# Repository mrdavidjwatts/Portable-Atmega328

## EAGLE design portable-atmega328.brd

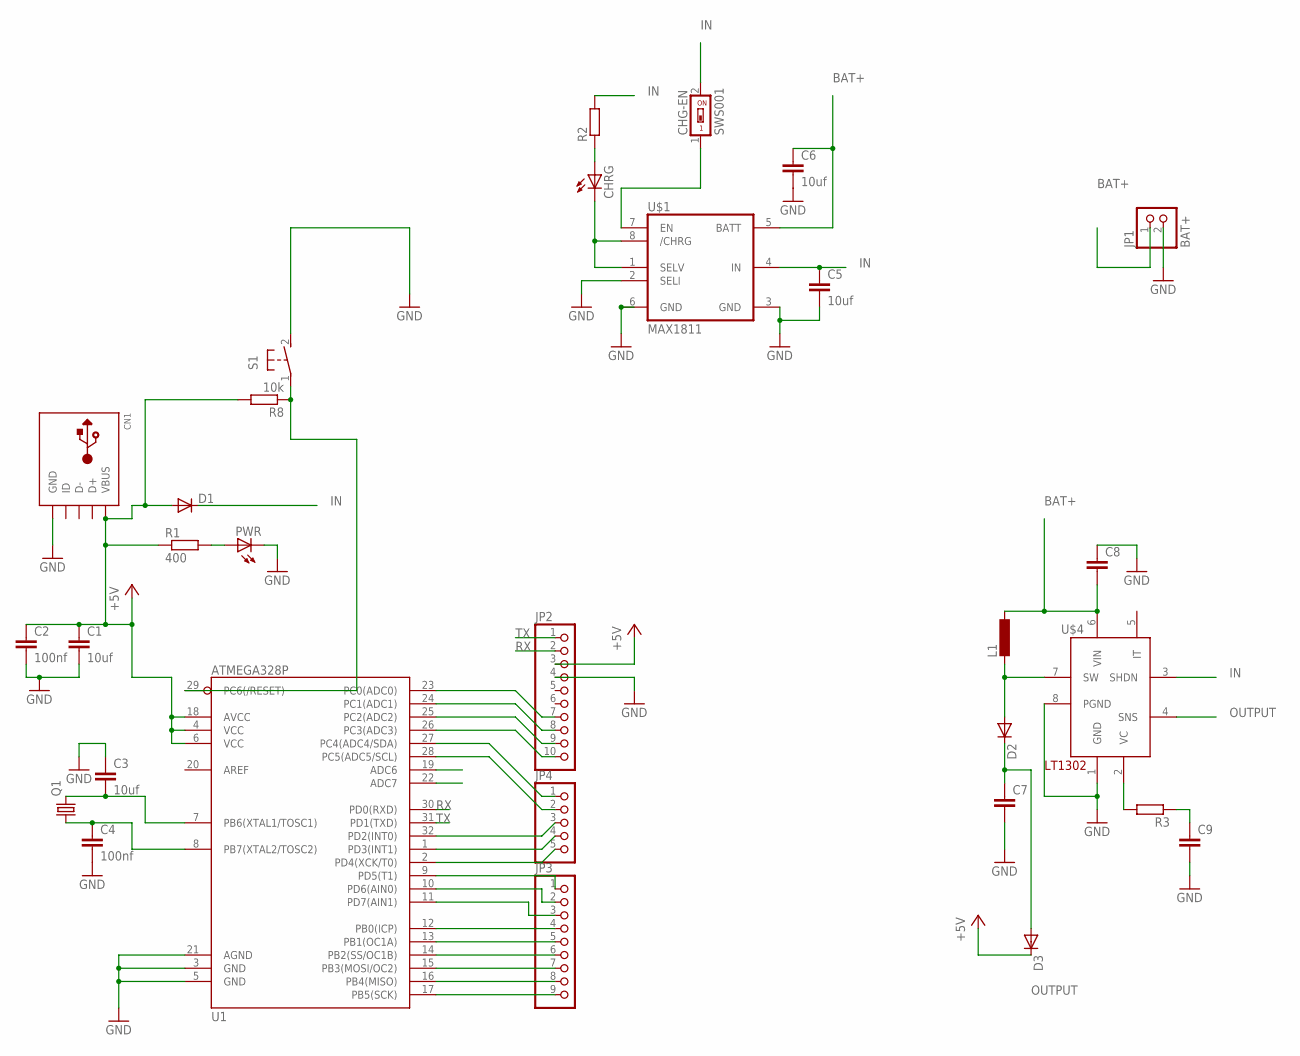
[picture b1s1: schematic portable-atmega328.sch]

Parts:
C1, C3, C5, C6: 10uf; C1206
C2, C4: 100nf; C1206
C7: C-EUC3225; C3225
C8, C9: C-EUC1206; C1206
CHG-EN: SWS001; SMS-001
CHRG: LEDCHIPLED_1206; CHIPLED_1206
CN1: USBMINIB; USB-MINIB
D1, D2, D3: DIODE-DO214AA; DO214AA
JP1: BAT+; 1X02
JP2: PINHD-1X10; 1X10
JP3: PINHD-1X9; 1X09
JP4: PINHD-1X5; 1X05
L1: DO3316P
PWR: LEDCHIPLED_1206; CHIPLED_1206
Q1: CRYSTALHC49S; HC49/S
R1: 400; R1206
R2, R3: R-EU_R1206; R1206
R8: 10k; R0805
S1: 31-XXSKINNY; B3F-31XX-SKINNIER
U1: ATMEGA328P; TQFP32-08
U$1: MAX1811; SO08
U$4: LT1302SO8; SO08

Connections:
+5V: C1.1, C2.1, CN1.VBUS, D1.A, D3.C, JP2.3, R1.1, R8.2, U1.4 (VCC), U1.6 (VCC), U1.18 (AVCC)
BAT+: C6.1, C8.2, JP1.1, L1.2, U$1.5 (BATT), U$4.6 (VIN)
GND: C1.2, C2.2, C3.1, C4.2, C5.2, C6.2, C7.2, C8.1, C9.2, CN1.GND, JP1.2, JP2.4, PWR.C, S1.2 (S), U1.3 (GND), U1.5 (GND), U1.21 (AGND), U$1.2 (SELI), U$1.3 (GND), U$1.6 (GND), U$4.1 (GND), U$4.8 (PGND)
IN: C5.1, CHG-EN.2, D1.C, R2.2, U$1.4 (IN), U$4.3 (SHDN)
unnamed: PWR.A, R1.2
unnamed: JP3.1, U1.9 (PD5(T1))
unnamed: C4.1, Q1.1, U1.8 (PB7(XTAL2/TOSC2))
unnamed: CHRG.C, U$1.1 (SELV), U$1.8 (/CHRG)
unnamed: CHRG.A, R2.1
unnamed: C3.2, Q1.2, U1.7 (PB6(XTAL1/TOSC1))
unnamed: CHG-EN.1, U$1.7 (EN)
unnamed: D2.A, L1.1, U$4.7 (SW)
unnamed: JP3.2, U1.10 (PD6(AIN0))
unnamed: JP3.3, U1.11 (PD7(AIN1))
unnamed: JP3.4, U1.12 (PB0(ICP))
unnamed: C9.1, R3.1
unnamed: R3.2, U$4.2 (VC)
unnamed: JP3.5, U1.13 (PB1(OC1A))
unnamed: JP3.6, U1.14 (PB2(SS/OC1B))
unnamed: JP3.7, U1.15 (PB3(MOSI/OC2))
unnamed: JP3.8, U1.16 (PB4(MISO))
unnamed: JP4.5, U1.2 (PD4(XCK/T0))
unnamed: JP4.4, U1.1 (PD3(INT1))
unnamed: JP4.3, U1.32 (PD2(INT0))
unnamed: JP4.2, U1.28 (PC5(ADC5/SCL))
unnamed: JP3.9, U1.17 (PB5(SCK))
unnamed: JP4.1, U1.27 (PC4(ADC4/SDA))
unnamed: JP2.10, U1.26 (PC3(ADC3))
unnamed: JP2.9, U1.25 (PC2(ADC2))
unnamed: JP2.8, U1.24 (PC1(ADC1))
unnamed: JP2.7, U1.23 (PC0(ADC0))
unnamed: R8.1, S1.1, U1.29 (PC6(/RESET))
OUTPUT: C7.1, D2.C, D3.A, U$4.4 (SNS)
RX: JP2.2, U1.30 (PD0(RXD))
TX: JP2.1, U1.31 (PD1(TXD))

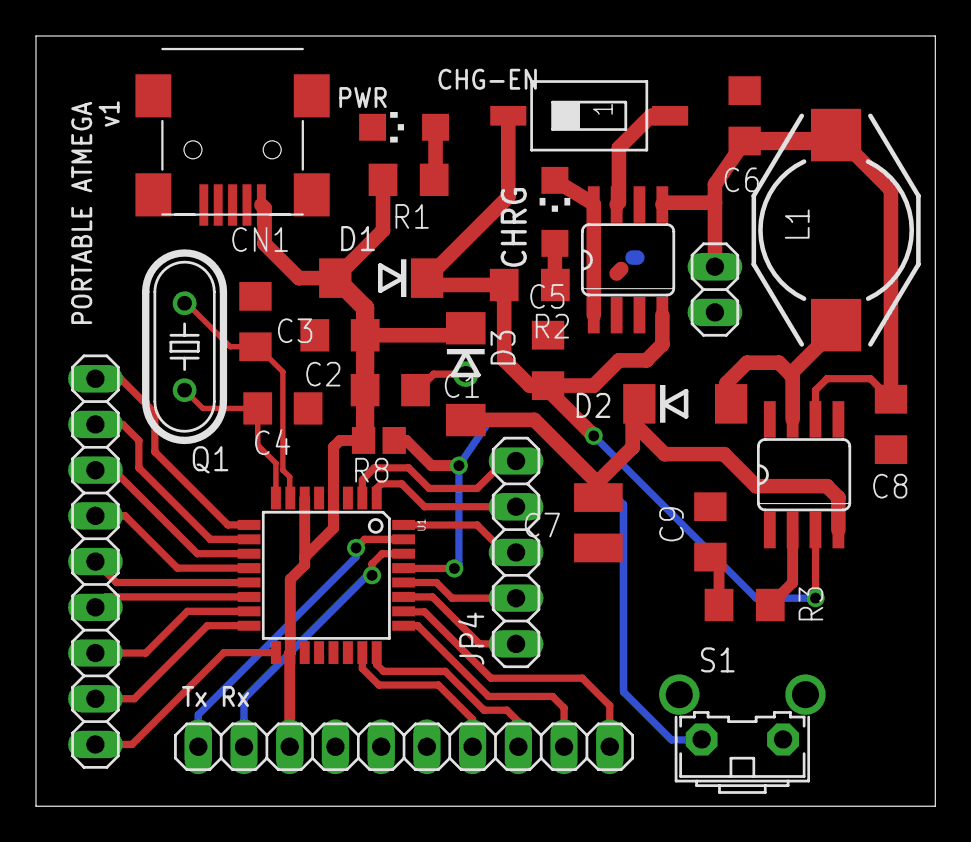
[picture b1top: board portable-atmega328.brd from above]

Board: 2 copper layers, 50.0 x 42.8 mm, 30 parts (0 on the bottom side), 35 nets.

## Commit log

2015-08-05 :boom::camel: Added .gitattributes & .gitignore files
2015-08-05 Board File
2015-08-05 Revert "Board File"
    This reverts commit ad277360ae9e2a07f9fcd133b2cbe83435900cac.
2015-08-05 Revert "Revert "Board File""
    This reverts commit eac3a3b66631548a77cb3644eb43b7db9d1d8764.

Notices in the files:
parts and their libraries:
SparkFun-DigitalIC: Licensing: Creative Commons ShareAlike 4.0 International - https://creativecommons.org/licenses/by-sa/4.0
